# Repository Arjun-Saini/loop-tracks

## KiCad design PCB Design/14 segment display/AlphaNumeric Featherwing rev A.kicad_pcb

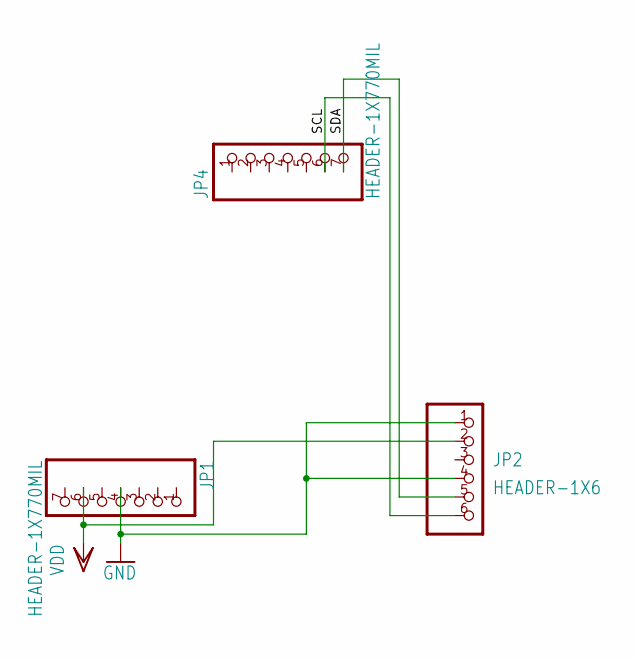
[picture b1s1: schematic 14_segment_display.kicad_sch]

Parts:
JP1, JP4: HEADER-1X770MIL; 1X07_ROUND_70
JP2: HEADER-1X6; 1X4-SMT

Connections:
/SCL: JP2.6, JP4.6
/SDA: JP2.5, JP4.7
GND: JP1.4, JP2.1, JP2.4
VDD: JP1.6, JP2.2

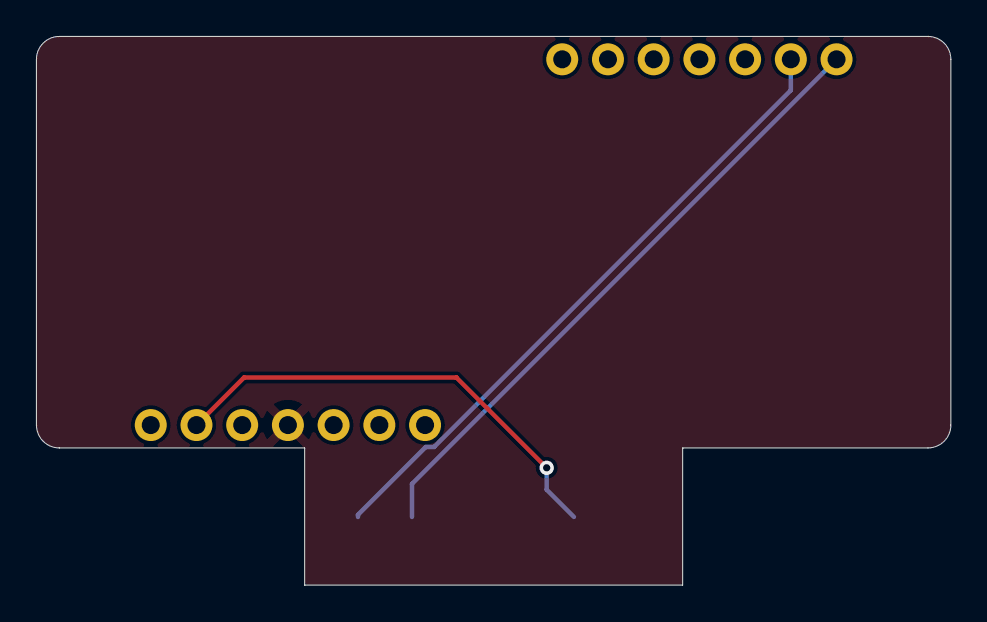
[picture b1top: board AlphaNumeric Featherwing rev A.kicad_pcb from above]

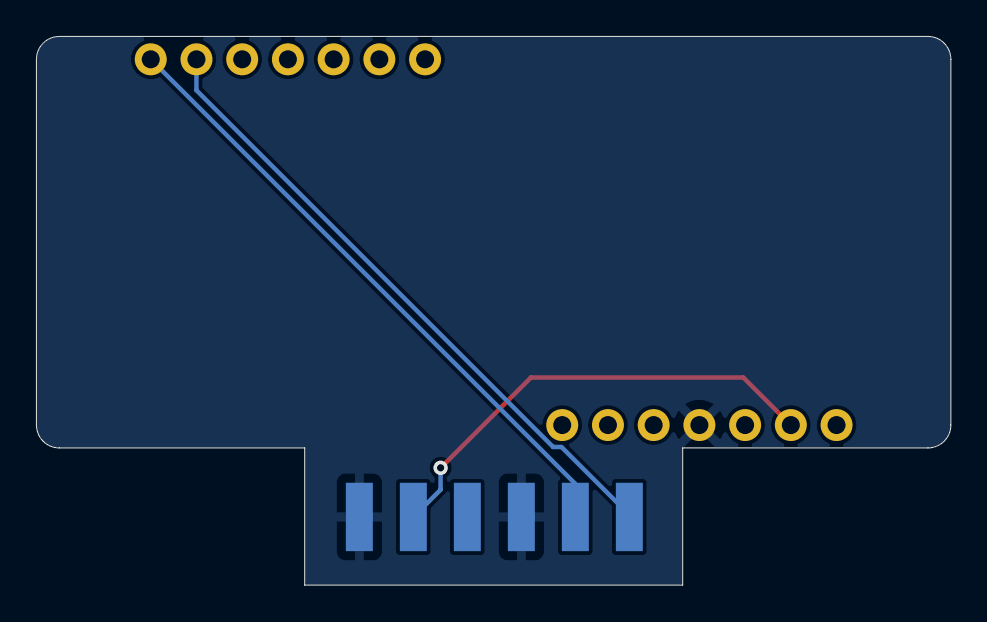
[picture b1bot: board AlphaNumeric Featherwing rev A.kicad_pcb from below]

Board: 16 copper layers, 50.8 x 30.5 mm, 3 parts (3 on the bottom side), 4 nets.

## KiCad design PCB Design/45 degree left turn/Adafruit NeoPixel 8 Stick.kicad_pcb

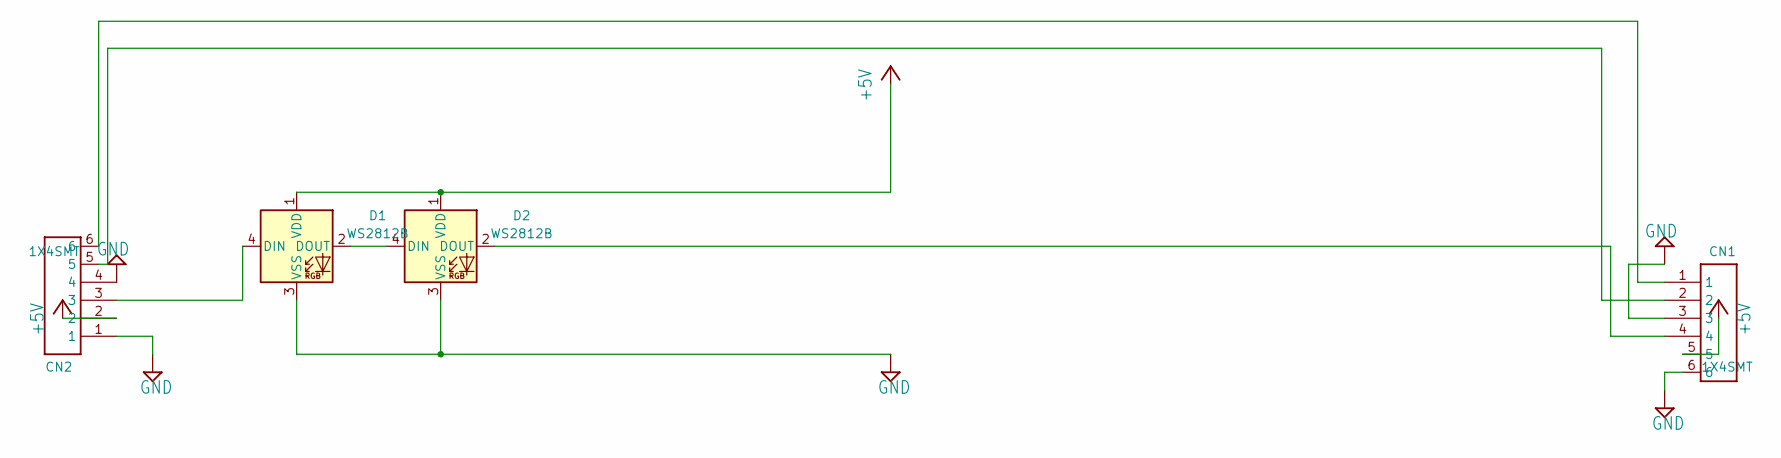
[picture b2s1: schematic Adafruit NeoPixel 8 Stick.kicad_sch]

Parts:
CN1, CN2: 1X4SMT; 1X4-SMT
D1, D2: WS2812B; LED_WS2812B_PLCC4_5.0x5.0mm_P3.2mm

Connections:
+5V: CN1.5, CN2.2, D1.1 (VDD), D2.1 (VDD)
GND: CN1.3, CN1.6, CN2.1, CN2.4, D1.3 (VSS), D2.3 (VSS)
unnamed: CN1.1, CN2.6
unnamed: CN1.2, CN2.5
unnamed: CN1.4, D2.2 (DOUT)
unnamed: CN2.3, D1.4 (DIN)
unnamed: D1.2 (DOUT), D2.4 (DIN)

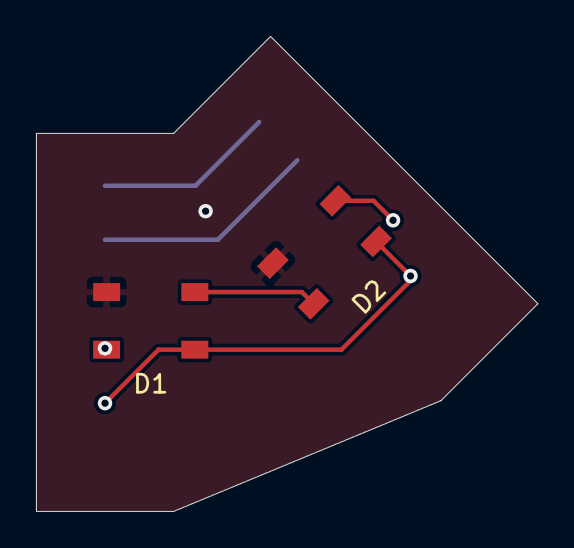
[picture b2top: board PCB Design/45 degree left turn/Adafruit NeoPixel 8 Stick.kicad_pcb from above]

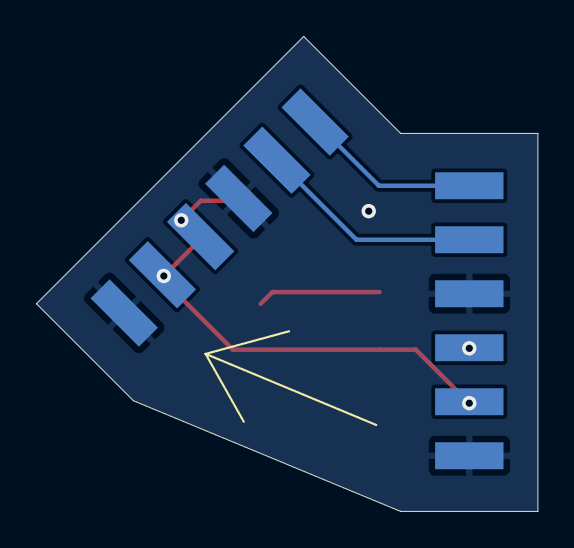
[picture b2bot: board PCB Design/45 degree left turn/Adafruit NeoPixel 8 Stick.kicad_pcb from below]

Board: 2 copper layers, 27.9 x 26.4 mm, 4 parts (2 on the bottom side), 7 nets.

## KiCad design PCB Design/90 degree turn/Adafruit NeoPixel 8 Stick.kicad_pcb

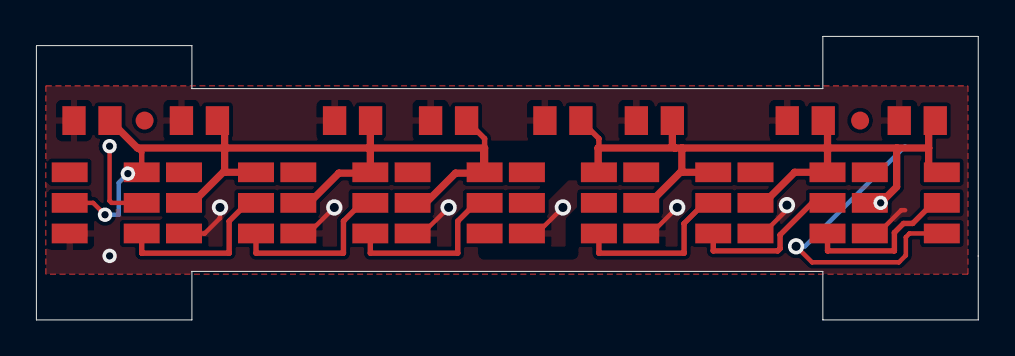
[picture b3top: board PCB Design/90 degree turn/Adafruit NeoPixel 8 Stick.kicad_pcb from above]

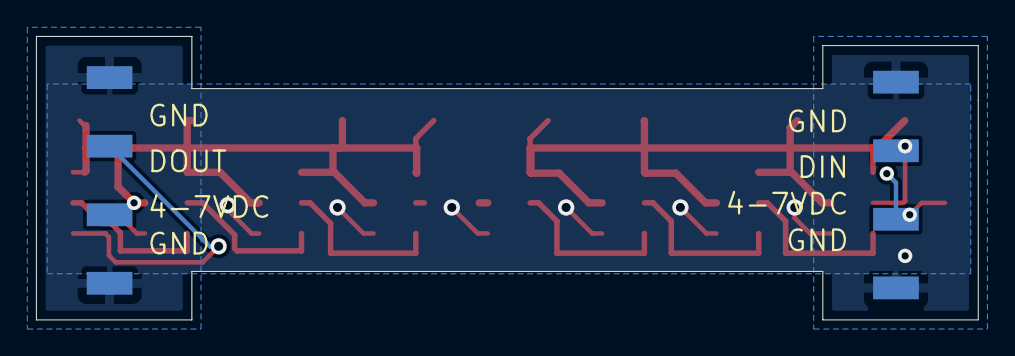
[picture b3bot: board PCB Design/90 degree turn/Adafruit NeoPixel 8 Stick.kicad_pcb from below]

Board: 2 copper layers, 52.3 x 15.7 mm, 20 parts (2 on the bottom side), 11 nets.

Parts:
C1, C2, C3, C4, C5, C6, C7, C8: C-USC0805K; C0805K
CN1, CN2: 1X4SMT; 1X4-SMT
FID1, FID3: FIDUCIAL""; FIDUCIAL_1MM
LED1, LED2, LED3, LED4, LED5, LED6, LED7, LED8: >VALUE; WS28115050

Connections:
+5V: C1.1, C2.1, C3.1, C4.1, C5.1, C6.1, C7.1, C8.1, CN1.3, CN2.2, LED1.LEDVDD, LED1.VDD, LED2.LEDVDD, LED2.VDD, LED3.LEDVDD, LED3.VDD, LED4.LEDVDD, LED4.VDD, LED5.LEDVDD, LED5.VDD, LED6.LEDVDD, LED6.VDD, LED7.LEDVDD, LED7.VDD, LED8.LEDVDD, LED8.VDD
GND: C1.2, C2.2, C3.2, C4.2, C5.2, C6.2, C7.2, C8.2, CN1.1, CN1.4, CN2.1, CN2.4, LED1.VSS (GND), LED2.VSS (GND), LED3.VSS (GND), LED4.VSS (GND), LED5.VSS (GND), LED6.VSS (GND), LED7.VSS (GND), LED8.VSS (GND)
unnamed: CN1.2, LED8.DO
unnamed: CN2.3, LED1.DI
unnamed: LED1.DO, LED2.DI
unnamed: LED2.DO, LED3.DI
unnamed: LED3.DO, LED4.DI
unnamed: LED4.DO, LED5.DI
unnamed: LED5.DO, LED6.DI
unnamed: LED6.DO, LED7.DI
unnamed: LED7.DO, LED8.DI

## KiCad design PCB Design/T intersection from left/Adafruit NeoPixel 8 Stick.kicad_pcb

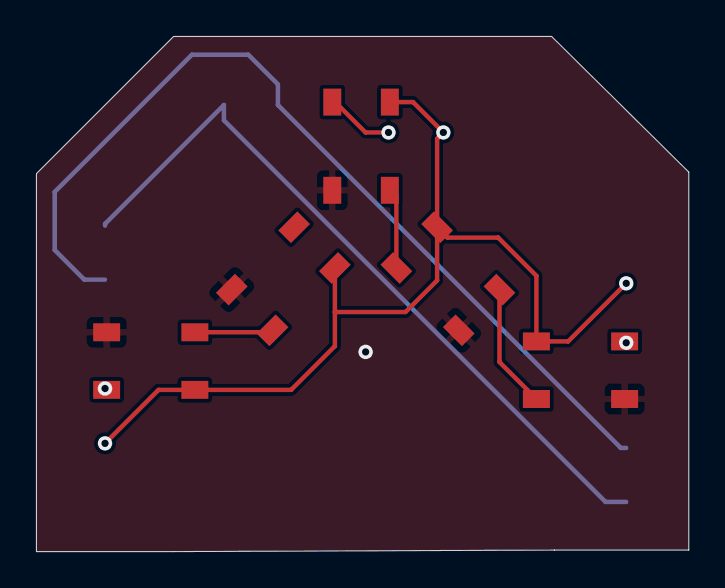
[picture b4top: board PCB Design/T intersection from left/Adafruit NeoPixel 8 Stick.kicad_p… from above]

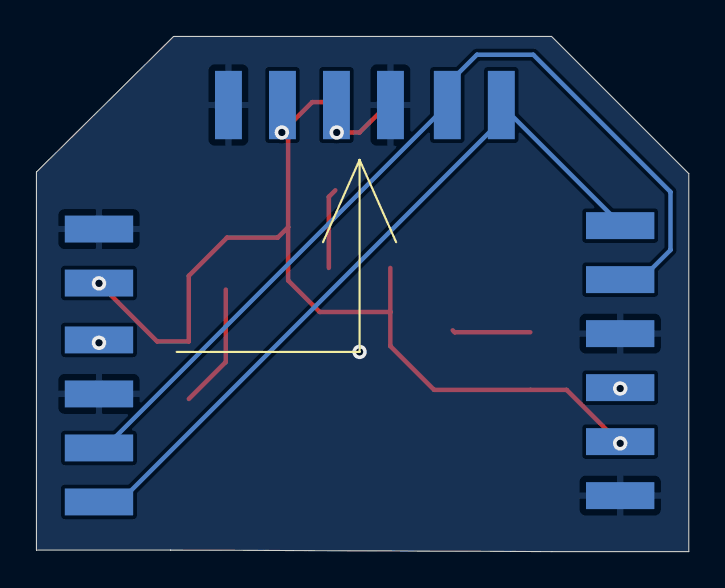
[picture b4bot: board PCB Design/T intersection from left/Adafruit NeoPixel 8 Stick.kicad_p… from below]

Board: 2 copper layers, 36.2 x 28.6 mm, 8 parts (3 on the bottom side), 10 nets.

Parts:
CN1, CN2, CN3: 1X4SMT; 1X4-SMT
D1, D2, D3, D4, D5: WS2812B; LED_WS2812B_PLCC4_5.0x5.0mm_P3.2mm

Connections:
+5V: CN1.5, CN2.2, CN3.2, D1.1 (VDD), D2.1 (VDD), D3.1 (VDD), D4.1 (VDD), D5.1 (VDD)
GND: CN1.3, CN1.6, CN2.1, CN2.4, CN3.1, CN3.4, D1.3 (VSS), D2.3 (VSS), D3.3 (VSS), D4.3 (VSS), D5.3 (VSS)
unnamed: CN1.1, CN2.6, CN3.6
unnamed: CN1.2, CN2.5, CN3.5
unnamed: CN1.4, D3.2 (DOUT)
unnamed: CN2.3, D1.4 (DIN)
unnamed: CN3.3, D4.4 (DIN)
unnamed: D1.2 (DOUT), D2.4 (DIN)
unnamed: D2.2 (DOUT), D3.4 (DIN)
unnamed: D4.2 (DOUT), D5.4 (DIN)

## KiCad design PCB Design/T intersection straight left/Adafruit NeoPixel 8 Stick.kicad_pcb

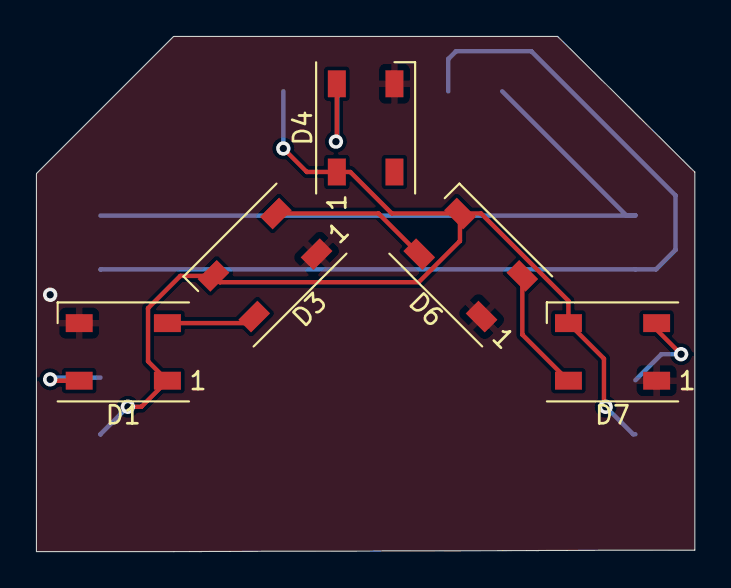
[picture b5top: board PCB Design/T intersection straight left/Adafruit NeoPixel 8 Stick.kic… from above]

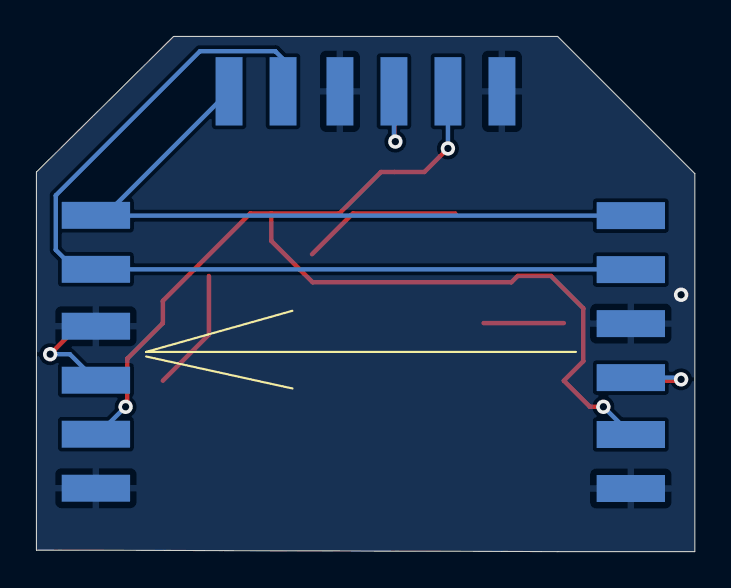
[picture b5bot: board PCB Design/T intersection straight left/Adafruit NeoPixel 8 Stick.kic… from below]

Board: 2 copper layers, 36.6 x 28.6 mm, 8 parts (3 on the bottom side), 10 nets.

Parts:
CN1, CN2, CN3: 1X4SMT; 1X4-SMT
D1, D3, D4, D6, D7: WS2812B; LED_WS2812B_PLCC4_5.0x5.0mm_P3.2mm

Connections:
+5V: CN1.5, CN2.2, CN3.5, D1.1 (VDD), D3.3 (VSS), D4.1 (VDD), D6.3 (VSS), D7.3 (VSS)
GND: CN1.3, CN1.6, CN2.1, CN2.4, CN3.3, CN3.6, D1.3 (VSS), D3.1 (VDD), D4.3 (VSS), D6.1 (VDD), D7.1 (VDD)
unnamed: CN1.1, CN2.6, CN3.1
unnamed: CN1.2, CN2.5, CN3.2
unnamed: CN1.4, D7.2 (DOUT)
unnamed: CN2.3, D1.4 (DIN)
unnamed: CN3.4, D4.4 (DIN)
unnamed: D1.2 (DOUT), D3.4 (DIN)
unnamed: D3.2 (DOUT), D6.4 (DIN)
unnamed: D6.2 (DOUT), D7.4 (DIN)
